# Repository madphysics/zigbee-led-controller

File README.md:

View this project on [CADLAB.io](https://cadlab.io/project/26827). 

# Zigbee LED Controller

A simple carrier card for driving some LEDs via PWM. Hosts an off the ZigBee module.

* Runs from 5V
* Derives 3v3 from 5V
* Has optional 12V rail for the PWM
* 4 channel, RGB+W low-side PWM

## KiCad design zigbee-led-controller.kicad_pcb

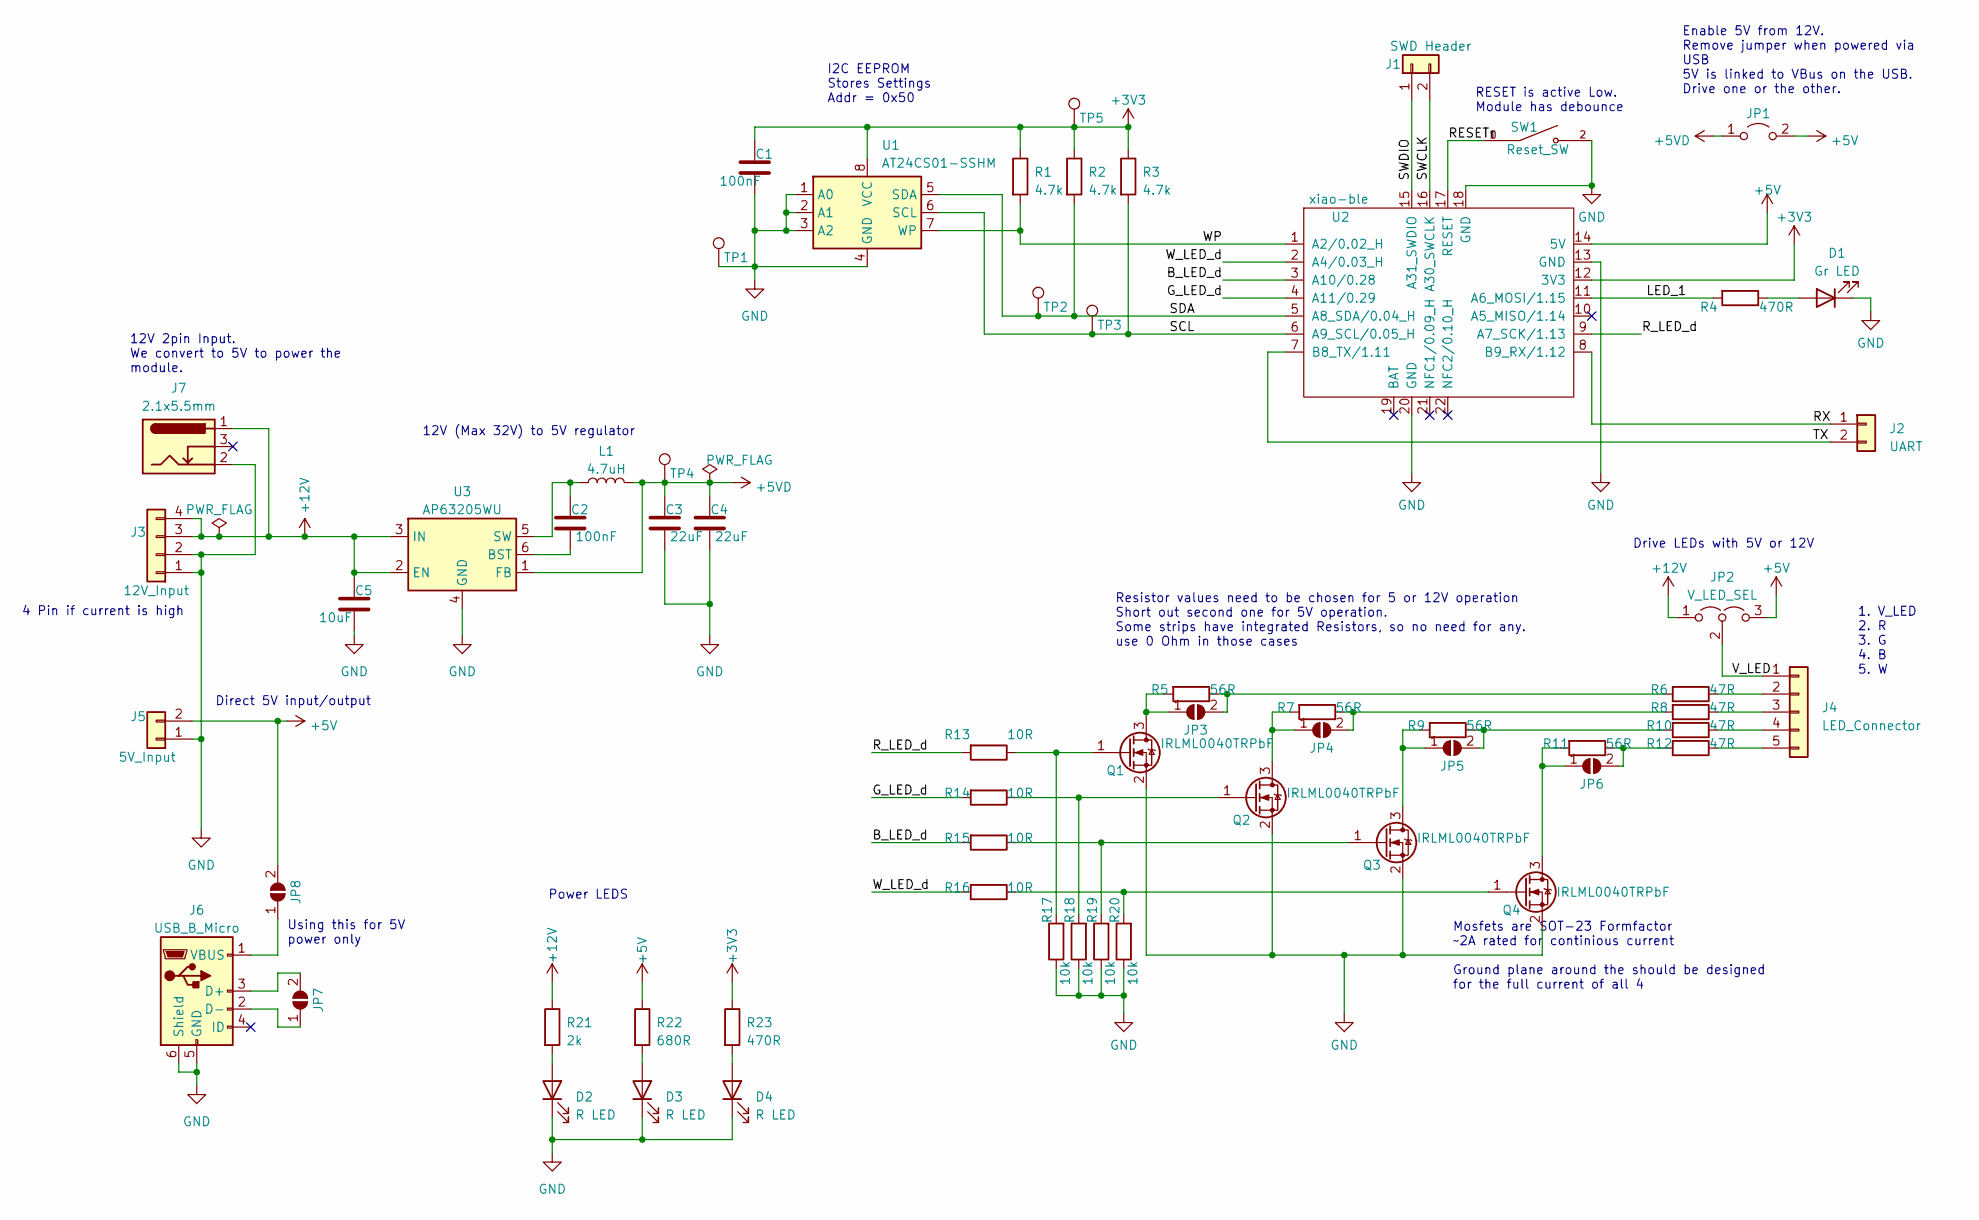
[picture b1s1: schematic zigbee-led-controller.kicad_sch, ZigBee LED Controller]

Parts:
C1, C2: 100nF; C_0603_1608Metric_Pad1.08x0.95mm_HandSolder
C3, C4: 22uF; C_0805_2012Metric_Pad1.18x1.45mm_HandSolder
C5: 10uF; C_0805_2012Metric_Pad1.18x1.45mm_HandSolder
D1: Gr LED; LED_0603_1608Metric_Pad1.05x0.95mm_HandSolder
D2, D3, D4: R LED; LED_0603_1608Metric_Pad1.05x0.95mm_HandSolder
J1: SWD Header; PinHeader_1x02_P2.54mm_Vertical
J2: UART; PinHeader_1x02_P2.54mm_Vertical
J3: 12V_Input; PinHeader_1x04_P2.54mm_Horizontal
J4: LED_Connector; PinHeader_1x05_P2.54mm_Vertical
J5: 5V_Input; PinHeader_1x02_P2.54mm_Horizontal
J6: USB_B_Micro; USB_Micro-B_Wuerth_629105150521
J7: 2.1x5.5mm; GRAVITECH_CON-SOCJ-2155
JP1: Jumper_2_Open; PinHeader_1x02_P2.54mm_Vertical
JP2: V_LED_SEL; PinHeader_1x03_P2.54mm_Vertical
JP3, JP4, JP5, JP6, JP7, JP8: Short; SolderJumper-2_P1.3mm_Open_RoundedPad1.0x1.5mm
L1: 4.7uH; L_Vishay_IHLP-1616
Q1, Q2, Q3, Q4: IRLML0040TRPbF; SOT-23-3
R1, R2, R3: 4.7k; R_0603_1608Metric_Pad0.98x0.95mm_HandSolder
R4, R23: 470R; R_0603_1608Metric_Pad0.98x0.95mm_HandSolder
R5, R7, R9, R11: 56R; R_0603_1608Metric_Pad0.98x0.95mm_HandSolder
R6, R8, R10, R12: 47R; R_0603_1608Metric_Pad0.98x0.95mm_HandSolder
R13, R14, R15, R16: 10R; R_0603_1608Metric_Pad0.98x0.95mm_HandSolder
R17, R18, R19, R20: 10k; R_0603_1608Metric_Pad0.98x0.95mm_HandSolder
R21: 2k; R_0603_1608Metric_Pad0.98x0.95mm_HandSolder
R22: 680R; R_0603_1608Metric_Pad0.98x0.95mm_HandSolder
SW1: Reset_SW; SW_B3U-1000P
TP1, TP2, TP3, TP4, TP5: TestPoint; TestPoint_Keystone_5000-5004_Miniature
U1: AT24CS01-SSHM; SOIC-8_3.9x4.9mm_P1.27mm
U2: xiao-ble; xiao-ble-smd-cutout
U3: AP63205WU; TSOT-23-6

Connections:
+3V3: C1.1, R1.1, R2.1, R3.1, R23.1, TP5.1, U1.8 (VCC), U2.12 (3V3); also elsewhere on the board
+5V: J5.2, JP1.2 (B), JP2.3 (B), JP8.2 (B), R22.1, U2.14 (5V)
+5VD: C3.1, C4.1, JP1.1 (A), L1.2, TP4.1, U3.1 (FB); also elsewhere on the board
+12V: C5.1, J3.3, J3.4, J7.1, JP2.1 (A), R21.1, U3.2 (EN), U3.3 (IN)
/B_LED_d: R15.2, U2.3 (A10/0.28)
/G_LED_d: R14.2, U2.4 (A11/0.29)
/LED_1: R4.2, U2.11 (A6_MOSI/1.15)
/RESETn: SW1.1, U2.17 (RESET); also elsewhere on the board
/RX: J2.1, U2.8 (B9_RX/1.12)
/R_LED_d: R13.2, U2.9 (A7_SCK/1.13)
/SCL: R3.2, TP3.1, U1.6 (SCL), U2.6 (A9_SCL/0.05_H); also elsewhere on the board
/SDA: R2.2, TP2.1, U1.5 (SDA), U2.5 (A8_SDA/0.04_H); also elsewhere on the board
/SWCLK: J1.2, U2.16 (A30_SWCLK)
/SWDIO: J1.1, U2.15 (A31_SWDIO)
/TX: J2.2, U2.7 (B8_TX/1.11)
/V_LED: J4.1, JP2.2 (C)
/WP: R1.2, U1.7 (WP), U2.1 (A2/0.02_H)
/W_LED_d: R16.2, U2.2 (A4/0.03_H)
GND: C1.2, C3.2, C4.2, C5.2, D1.1 (K), D2.1 (K), D3.1 (K), D4.1 (K), J3.1, J3.2, J5.1, J6.5 (GND), J6.6 (Shield), J7.2, Q1.2 (S), Q2.2 (S), Q3.2 (S), Q4.2 (S), R17.1, R18.1, R19.1, R20.1, SW1.2, TP1.1, U1.1 (A0), U1.2 (A1), U1.3 (A2), U1.4 (GND), U2.13 (GND), U2.18 (GND), U2.20 (GND), U3.4 (GND); also elsewhere on the board
unnamed: D1.2 (A), R4.1
unnamed: D2.2 (A), R21.2
unnamed: D3.2 (A), R22.2
unnamed: D4.2 (A), R23.2
unnamed: J4.2, R6.1
unnamed: J4.3, R8.1
unnamed: J4.4, R10.1
unnamed: J4.5, R12.1
unnamed: J6.3 (D+), JP7.2 (B)
unnamed: J6.2 (D-), JP7.1 (A)
unnamed: J6.1 (VBUS), JP8.1 (A)
unnamed: JP3.1 (A), Q1.3 (D), R5.2
unnamed: JP3.2 (B), R5.1, R6.2
unnamed: JP4.1 (A), Q2.3 (D), R7.2
unnamed: JP4.2 (B), R7.1, R8.2
unnamed: JP5.1 (A), Q3.3 (D), R9.2
unnamed: JP5.2 (B), R9.1, R10.2
unnamed: JP6.1 (A), Q4.3 (D), R11.2
unnamed: JP6.2 (B), R11.1, R12.2
unnamed: Q1.1 (G), R13.1, R17.2
unnamed: Q2.1 (G), R14.1, R18.2
unnamed: Q3.1 (G), R15.1, R19.2
unnamed: Q4.1 (G), R16.1, R20.2
unnamed: C2.2, U3.6 (BST)
unnamed: C2.1, L1.1, U3.5 (SW)

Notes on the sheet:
12V 2pin Input. We convert to 5V to power the module.
1. V_LED 2. R 3. G 4. B 5. W
I2C EEPROM Stores Settings Addr = 0x50
Power LEDS
Resistor values need to be chosen for 5 or 12V operation Short out second one for 5V operation. Some strips have integrated Resistors, so no need for any. use 0 Ohm in those cases
Enable 5V from 12V. Remove jumper when powered via USB 5V is linked to VBus on the USB. Drive one or the other.
Direct 5V input/output
12V (Max 32V) to 5V regulator
Using this for 5V power only
Mosfets are SOT-23 Formfactor ~2A rated for continious current Ground plane around the should be designed for the full current of all 4
Drive LEDs with 5V or 12V
4 Pin if current is high
RESET is active Low. Module has debounce

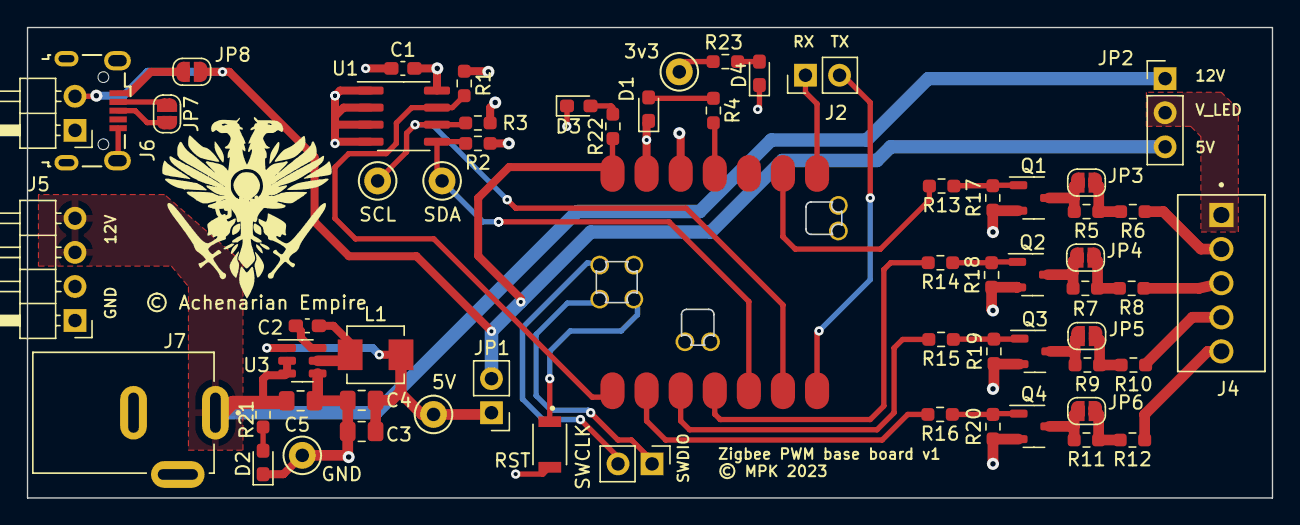
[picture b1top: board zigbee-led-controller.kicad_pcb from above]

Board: 2 copper layers, 92.7 x 35.0 mm, 61 parts (0 on the bottom side), 44 nets.

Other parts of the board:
3v3, 5V: TestPoint; TestPoint_Keystone_5000-5004_Miniature
GND: TestPoint; TestPoint_Keystone_5000-5004_Miniature
RST: Reset_SW; SW_B3U-1000P
SCL: TestPoint; TestPoint_Keystone_5000-5004_Miniature
SDA: TestPoint; TestPoint_Keystone_5000-5004_Miniature

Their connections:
+3V3: 3v3.1; also elsewhere on the board
+5VD: 5V.1; also elsewhere on the board
/RESETn: RST.1; also elsewhere on the board
/SCL: SCL.1; also elsewhere on the board
/SDA: SDA.1; also elsewhere on the board
GND: GND.1, RST.2; also elsewhere on the board

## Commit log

2023-04-01 Update gitignore files
2023-04-01 First pass at the schemaics
2023-04-01 PDF of first schematic
2023-04-01 Todo list added
2023-04-02 Added GRAVITECH_CON-SOCJ-2155 footprint for the barrel connector.
2023-04-02 Update todo
2023-04-02 3d modules added
2023-04-02 Datasheet/pins added
2023-04-02 PCB Initial placement
2023-04-07 Routing done, first pass anyway.
2023-04-11 Library updates
2023-04-11 Updated some footprints and finalized layout. Added better output connector and rst switch
2023-04-11 Gerber outputs
2023-04-22 Updated, given to pcbway to quote
2023-04-22 Backlink to CADLAB.io has been added.
2023-04-26 New 3d image
2023-04-26 Shrink image!
2023-04-26 Added image to Readme

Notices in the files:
zigbee-led-controller.kicad_pcb:
© MPK 2023
parts and their libraries:
© Achenarian Empire
